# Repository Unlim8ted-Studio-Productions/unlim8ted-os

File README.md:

<div align="center">
<h1>Unlim8ted Phone</h1><p>A custom CM4-based handheld phone project</p>

<br>

<table>
<tr>

<td width="50%">
  
</td>

<td width="50%">
  
</td>

</tr>
</table>

</div>

---

<h2>Overview</h2>

<p>
Unlim8ted Phone is a handheld phone project built around the Raspberry Pi Compute Module 4.
</p>

<p>
This repository contains the hardware, enclosure design, operating system work, and archived PCB development files for the project.
</p>

---

<h2>Repository Layout</h2>

```text
/
├─ 3d/        enclosure, renders, printable parts
├─ docs/      project documentation
├─ os/        Unlim8ted OS source and docs
├─ pcb/       archived PCB design files
└─ README.md
```

---

<h2>Hardware + Cost Breakdown</h2>

<table>

<tr>
<th align="left">Component</th>
<th align="left">Details</th>
<th align="right">Price</th>
</tr>

<tr>
<td>Compute Module</td>
<td>Raspberry Pi CM4 Lite — 8GB RAM</td>
<td align="right">$105.00</td>
</tr>

<tr>
<td>Carrier Board</td>
<td>Waveshare CM4-NANO-C</td>
<td align="right">$29.99</td>
</tr>

<tr>
<td>Display</td>
<td>Waveshare 6.25-inch DSI LCD</td>
<td align="right">$59.99</td>
</tr>

<tr>
<td>Storage</td>
<td>32GB microSD card</td>
<td align="right">$20.00</td>
</tr>

<tr>
<td>Power Board</td>
<td>Seeed LiPo Rider Plus</td>
<td align="right">$4.90</td>
</tr>

<tr>
<td>Battery</td>
<td>3.7V 3000mAh LiPo</td>
<td align="right">$12.49</td>
</tr>

<tr>
<td>Display Cable</td>
<td>15cm double-sided 15-pin DSI cable</td>
<td align="right">Included</td>
</tr>

<tr>
<td>USB Cable</td>
<td>Adafruit USB Type A → USB Type C</td>
<td align="right">$2.95</td>
</tr>

</table>

<br>

<div align="center">

<h1>$235.32</h1>

<sub>Current estimated build total</sub>

</div>

---

<h2>PCB Status</h2>

<p>
The PCB files inside <code>/pcb</code> are archived only.
</p>

<p>
The original custom PCB revision was abandoned in favor of already-manufactured off-the-shelf boards.
</p>

<p>
These files are preserved strictly for reference purposes and should not be used for fabrication or assembly.
</p>

---

<h2>Project Links</h2>

<div align="center">

<a href="./docs/">Documentation</a>

<a href="./os/">OS Source</a>

<a href="./3d/">3D Files</a>

<a href="./pcb/">Archived PCB Files</a>

</div>

---

<div align="center">

<h3>Unlim8ted Studios</h3>

</div>

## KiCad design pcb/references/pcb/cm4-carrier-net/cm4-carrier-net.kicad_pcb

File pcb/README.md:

# PCB Folder

This folder contains outdated and unfinished PCB design work, archived revisions, fabrication output, supporting libraries, and reference material for the phone project. None of the custom PCB files should be fabricated, and ignoring this warning could result in damage.

## Layout

- `custom pcb files/`
  - the KiCad project folders and board files
  - currently includes `phone/`, `phone-part-1/`, and `phone6layer/`
- `libraries/`
  - custom symbol and footprint libraries
  - vendor library imports used by the projects
- `models/`
  - component, enclosure, and vendor-supplied 3D assets
- `fabrication/`
  - gerbers, pick-and-place files, plots, and JLCPCB exports
- `references/`
  - datasheets, diagrams, screenshots, and video captures
- `scripts/`
  - helper scripts used alongside the PCB workflow
- `archives/`
  - backups, candidate revisions, zip bundles, and superseded files

## Working Projects

- `custom pcb files/phone/`
  - main phone schematic project and its exported 3D artifacts
- `custom pcb files/phone6layer/`
  - 6-layer phone board revision
- `custom pcb files/phone-part-1/`
  - partial board split-out

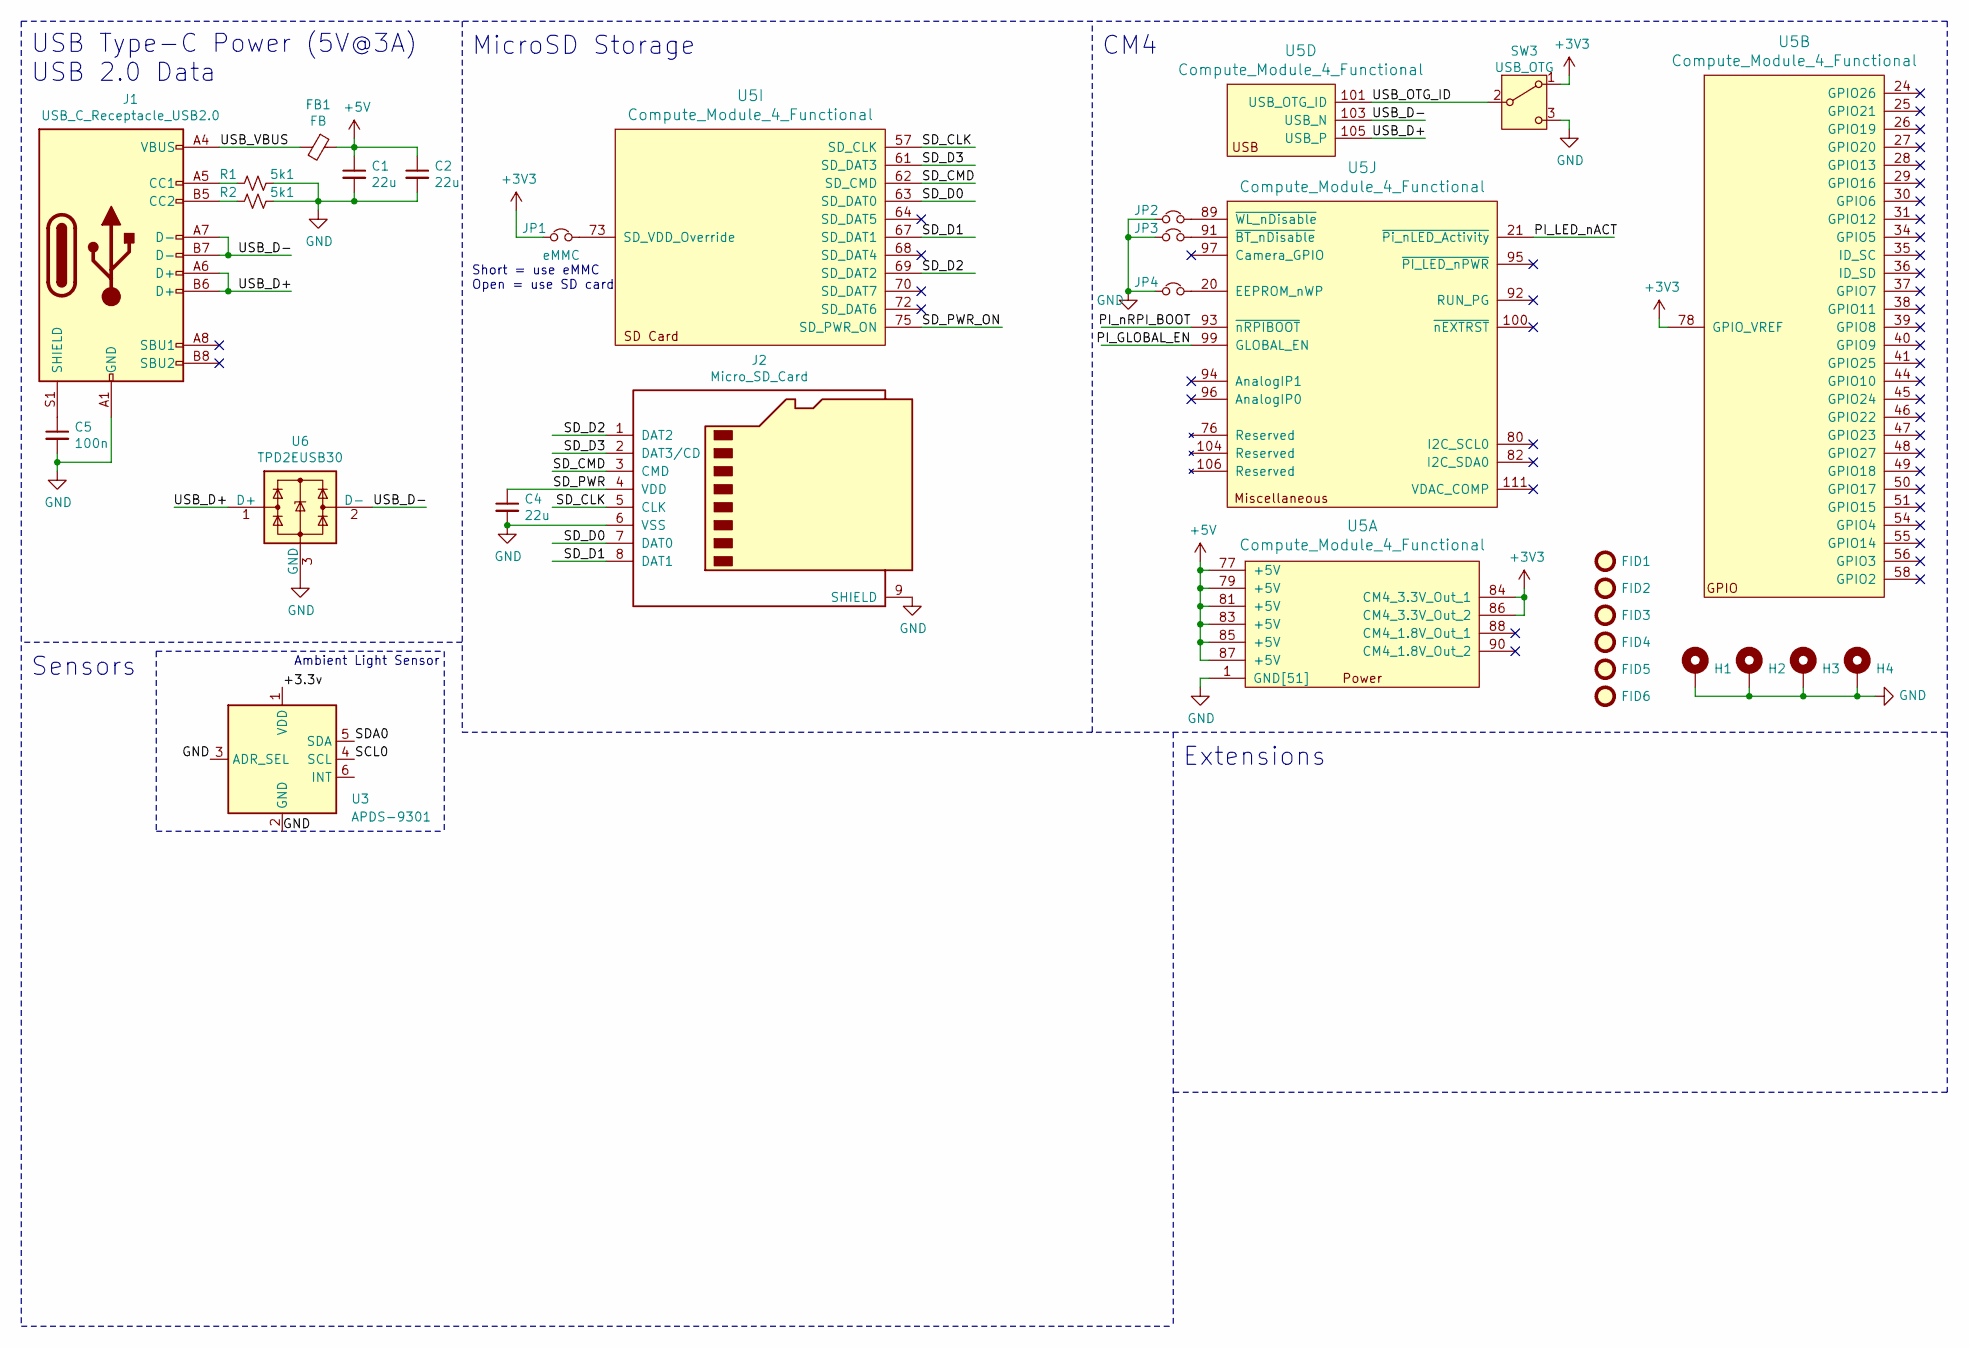
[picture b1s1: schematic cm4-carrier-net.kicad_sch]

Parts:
C1, C2, C4: 22u; C_0805_2012Metric
C5: 100n; C_0805_2012Metric
FB1: FB; L_0805_2012Metric
FID1, FID2, FID3, FID4, FID5, FID6: Fiducial; Fiducial_0.75mm_Mask1.5mm
H1, H2, H3, H4: MountingHole_Pad; MountingHole_2.7mm_M2.5_Pad_Via
J1: USB_C_Receptacle_USB2.0; USB_C_Receptacle_GCT-USB4105
J2: Micro_SD_Card; microSD_HC_Molex_104031-0811
JP1: eMMC; J_Small_NC
JP2: ~WL_nDisable; J_Small_NC
JP3: ~BT_nDisable; J_Small_NC
JP4: EEPROM_nWP; J_Small_NC
R1, R2: 5k1; R_0603_1608Metric
SW3: USB_OTG; SW_SPDT_CK-JS102011SAQN
U3: APDS-9301; Broadcom_APDS-9301
U5: Compute_Module_4_Functional; Raspberry-Pi-4-Compute-Module
U6: TPD2EUSB30; Texas_DRT-3

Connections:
+3V3: JP1.1, SW3.1 (A), U5.78 (GPIO_VREF), U5.84 (CM4_3.3V_Out_1), U5.86 (CM4_3.3V_Out_2)
+5V: C1.1, C2.1, FB1.1, U5.77 (+5V), U5.79 (+5V), U5.81 (+5V), U5.83 (+5V), U5.85 (+5V), U5.87 (+5V)
/+3.3v: U3.1 (VDD)
/PI_GLOBAL_EN: U5.99 (GLOBAL_EN)
/PI_LED_nACT: U5.21 (~Pi_nLED_Activity)
/PI_nRPI_BOOT: U5.93 (~nRPIBOOT)
/SCL0: U3.4 (SCL)
/SDA0: U3.5 (SDA)
/SD_CLK: J2.5 (CLK), U5.57 (SD_CLK)
/SD_CMD: J2.3 (CMD), U5.62 (SD_CMD)
/SD_D0: J2.7 (DAT0), U5.63 (SD_DAT0)
/SD_D1: J2.8 (DAT1), U5.67 (SD_DAT1)
/SD_D2: J2.1 (DAT2), U5.69 (SD_DAT2)
/SD_D3: J2.2 (DAT3/CD), U5.61 (SD_DAT3)
/SD_PWR: C4.1, J2.4 (VDD)
/SD_PWR_ON: U5.75 (SD_PWR_ON)
/USB_D+: J1.A6 (D+), J1.B6 (D+), U5.105 (USB_P), U6.1 (D+)
/USB_D-: J1.A7 (D-), J1.B7 (D-), U5.103 (USB_N), U6.2 (D-)
/USB_OTG_ID: SW3.2 (B), U5.101 (USB_OTG_ID)
/USB_VBUS: FB1.2, J1.A4 (VBUS), J1.A9 (VBUS), J1.B4 (VBUS), J1.B9 (VBUS)
GND: C1.2, C2.2, C4.2, C5.2, H1.1, H2.1, H3.1, H4.1, J1.A1 (GND), J1.A12 (GND), J1.B1 (GND), J1.B12 (GND), J2.6 (VSS), J2.9 (SHIELD), JP2.1, JP3.1, JP4.1, R1.1, R2.1, SW3.3 (C), U3.2 (GND), U3.3 (ADR_SEL), U5.1 (GND[51]), U5.2 (GND[51]), U5.7 (GND[51]), U5.8 (GND[51]), U5.13 (GND[51]), U5.14 (GND[51]), U5.22 (GND[51]), U5.23 (GND[51]), U5.32 (GND[51]), U5.33 (GND[51]), U5.42 (GND[51]), U5.43 (GND[51]), U5.52 (GND[51]), U5.53 (GND[51]), U5.59 (GND[51]), U5.60 (GND[51]), U5.65 (GND[51]), U5.66 (GND[51]), U5.71 (GND[51]), U5.74 (GND[51]), U5.98 (GND[51]), U5.107 (GND[51]), U5.108 (GND[51]), U5.113 (GND[51]), U5.114 (GND[51]), U5.119 (GND[51]), U5.120 (GND[51]), U5.125 (GND[51]), U5.126 (GND[51]), U5.131 (GND[51]), U5.132 (GND[51]), U5.137 (GND[51]), U5.138 (GND[51]), U5.144 (GND[51]), U5.150 (GND[51]), U5.155 (GND[51]), U5.156 (GND[51]), U5.161 (GND[51]), U5.162 (GND[51]), U5.167 (GND[51]), U5.168 (GND[51]), U5.173 (GND[51]), U5.174 (GND[51]), U5.179 (GND[51]), U5.180 (GND[51]), U5.185 (GND[51]), U5.186 (GND[51]), U5.191 (GND[51]), U5.192 (GND[51]), U5.197 (GND[51]), U5.198 (GND[51]), U6.3 (GND)
unnamed: J1.A5 (CC1), R1.2
unnamed: J1.B5 (CC2), R2.2
unnamed: C5.1, J1.S1 (SHIELD)
unnamed: JP1.2, U5.73 (SD_VDD_Override)
unnamed: JP4.2, U5.20 (EEPROM_nWP)
unnamed: JP3.2, U5.91 (~BT_nDisable)
unnamed: JP2.2, U5.89 (~WL_nDisable)

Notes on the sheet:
MicroSD Storage
USB Type-C Power (5V@3A) USB 2.0 Data
Sensors
Ambient Light Sensor
Extensions
CM4
Short = use eMMC Open = use SD card

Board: 4 copper layers, 27 parts (9 on the bottom side), 21 nets, no tracks yet.

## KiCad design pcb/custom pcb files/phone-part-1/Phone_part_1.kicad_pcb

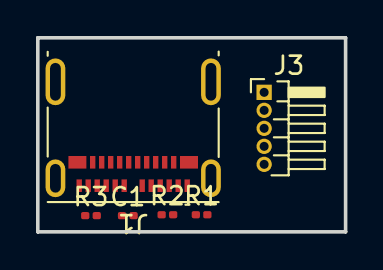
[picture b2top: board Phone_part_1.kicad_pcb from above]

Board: 2 copper layers, 17.1 x 10.8 mm, 6 parts (0 on the bottom side), 7 nets, no tracks yet.

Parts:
C1: 10uF; C_0201_0603Metric
J1: USB_C_Receptacle; USB_C_Receptacle_Molex_105450-0101
J3: Conn_01x05_Pin; PinHeader_1x05_P1.00mm_Horizontal
R1, R2: 5.1K; R_0201_0603Metric
R3: 0 Ω; R_0201_0603Metric

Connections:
/+5v: C1.1, J1.A4 (VBUS), J1.A9 (VBUS), J1.B4 (VBUS), J1.B9 (VBUS), J3.1
/AIN0: J1.A5 (CC1), R1.1
/AIN1: J1.B5 (CC2), R2.1
/USB2_N: J1.A7 (D-), J1.B7 (D-), J3.3
/USB2_P: J1.A6 (D+), J1.B6 (D+), J3.4
GND: C1.2, J1.A1 (GND), J1.A12 (GND), J1.B1 (GND), J1.B12 (GND), J3.2, J3.5, R1.2, R2.2, R3.2
unnamed: J1.S1 (SHIELD), R3.1

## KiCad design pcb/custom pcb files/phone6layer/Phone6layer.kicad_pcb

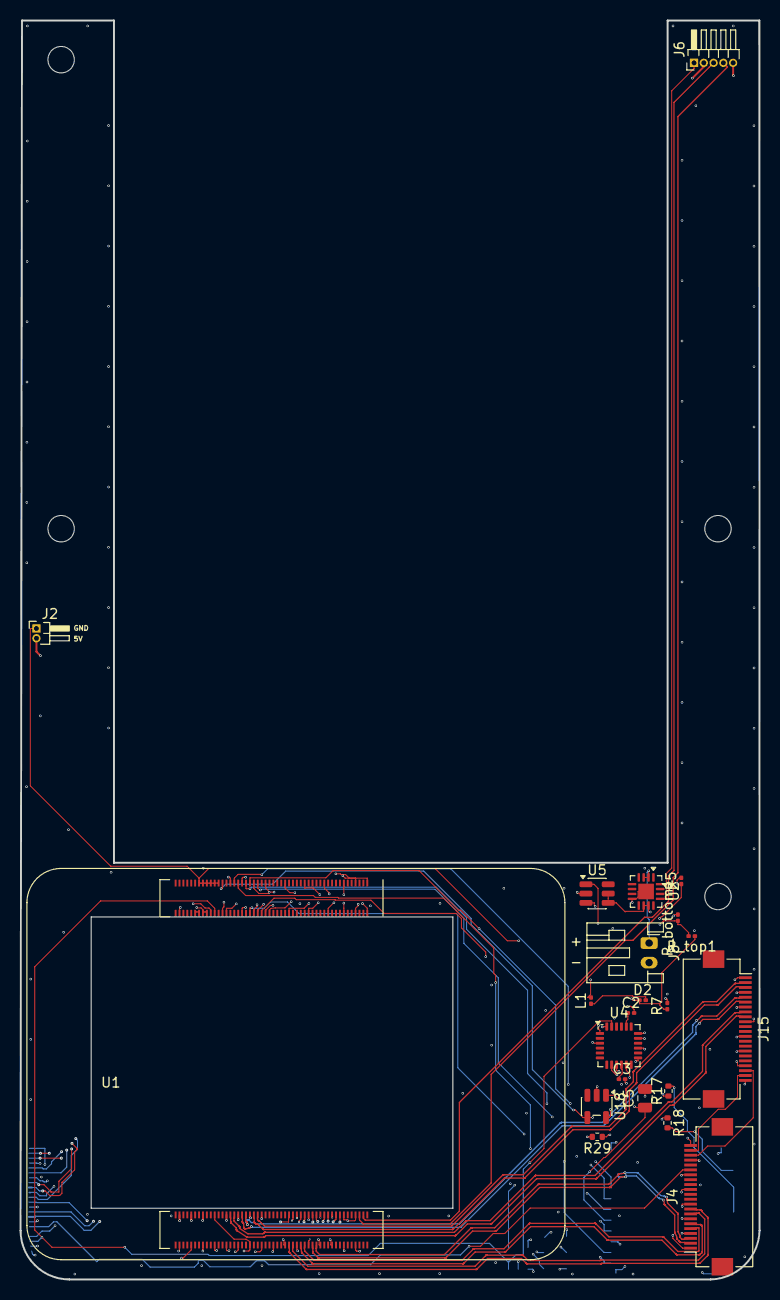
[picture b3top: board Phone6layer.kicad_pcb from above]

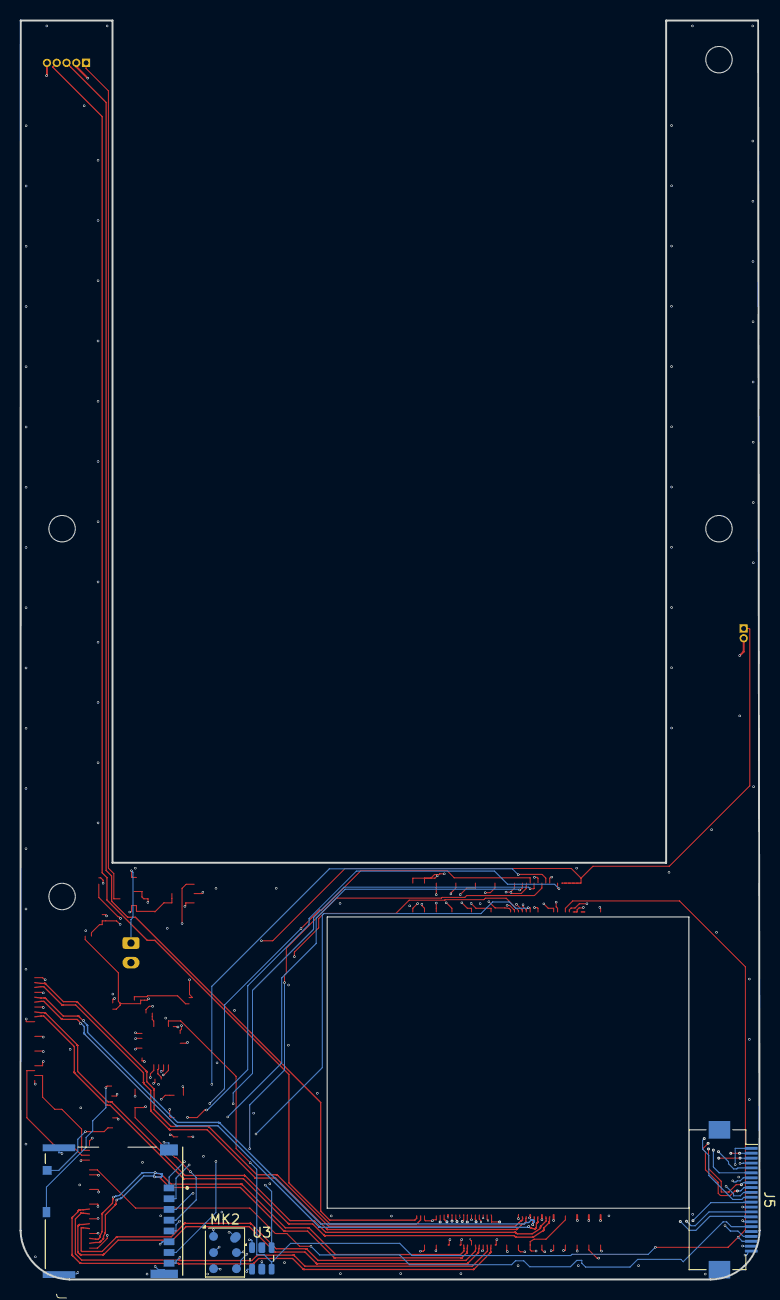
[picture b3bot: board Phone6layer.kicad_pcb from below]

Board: 6 copper layers, 75.5 x 128.7 mm, 26 parts (4 on the bottom side), 55 nets.

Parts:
C2: 2.2 nF; C_0201_0603Metric
C3: 0.1 µF; C_0201_0603Metric
C5: 10u; C_0805_2012Metric
D2: D; D_0201_0603Metric
J2: Conn_01x04_Pin; PinHeader_1x02_P1.00mm_Horizontal
J4, J5, J15: Conn_01x22_Female; Hirose_FH12-22S-0.5SH_1x22-1MP_P0.50mm_Horizontal
J6: Conn_01x05_Pin; PinHeader_1x05_P1.00mm_Horizontal
J7: Micro_SD_Card_Det; SDCARD_MOLEX_503398-1892
J8: Conn_01x02; JST_PH_S2B-PH-K_1x02_P2.00mm_Horizontal
L1: L; L_0201_0603Metric
MK2: MP45DT02; ST_HLGA-6_3.76x4.72mm_P1.65mm
R5, R7: 22 µF; R_0201_0603Metric
R17, R18: nf; R_0402_1005Metric
R29: 12K 1%; R_0402_1005Metric
R_bottom1: 15 kΩ; R_0201_0603Metric
R_top1: 110 kΩ; R_0201_0603Metric
U1: ComputeModule4; Raspberry-Pi-4-Compute-Module-Connector-Phone-Modified
U2: BQ24074RGT; VQFN-16-1EP_3x3mm_P0.5mm_EP1.6x1.6mm
U3: APDS-9301; Broadcom_APDS-9301
U4: MPU-9150; InvenSense_QFN-24_4x4mm_P0.5mm
U5: MT3608; SOT-23-6
U18: RT9742GGJ5; SOT-23-5

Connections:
/+1.8v: U1.88 (+1.8v_(Output)), U1.90 (+1.8v_(Output))
/+3.3v: J4.22, J5.22, J15.22, MK2.6 (VDD), R17.1, R29.1, U1.84 (+3.3v_(Output)), U1.86 (+3.3v_(Output)), U3.1 (VDD), U4.3 (VDD), U4.8 (VLOGIC), U4.13 (VDD), U18.5 (IN)
/+5v: D2.1 (K), J2.1, R7.1, R_top1.1, U1.77 (+5v_(Input)), U1.79 (+5v_(Input)), U1.81 (+5v_(Input)), U1.83 (+5v_(Input)), U1.85 (+5v_(Input)), U1.87 (+5v_(Input))
/CAM0_C_N: J4.8, U1.140 (CAM0_C_N)
/CAM0_C_P: J4.9, U1.142 (CAM0_C_P)
/CAM0_D0_N: J4.2, U1.128 (CAM0_D0_N)
/CAM0_D0_P: J4.3, U1.130 (CAM0_D0_P)
/CAM0_D1_N: J4.5, U1.134 (CAM0_D1_N)
/CAM0_D1_P: J4.6, U1.136 (CAM0_D1_P)
/CAM1_C_N: J5.8, U1.127 (CAM1_C_N)
/CAM1_C_P: J5.9, U1.129 (CAM1_C_P)
/CAM1_D0_N: J5.2, U1.115 (CAM1_D0_N)
/CAM1_D0_P: J5.3, U1.117 (CAM1_D0_P)
/CAM1_D1_N: J5.5, U1.121 (CAM1_D1_N)
/CAM1_D1_P: J5.6, U1.123 (CAM1_D1_P)
/CAM1_D2_N: J5.11, U1.133 (CAM1_D2_N)
/CAM1_D2_P: J5.12, U1.135 (CAM1_D2_P)
/CAM1_D3_N: J5.14, U1.139 (CAM1_D3_N)
/CAM1_D3_P: J5.15, U1.141 (CAM1_D3_P)
/CAM_GPIO: J4.17, J5.17
/DSI0_C_N: J15.8, U1.169 (DSI0_C_N)
/DSI0_C_P: J15.9, U1.171 (DSI0_C_P)
/DSI0_D0_N: J15.2, U1.157 (DSI0_D0_N)
/DSI0_D0_P: J15.3, U1.159 (DSI0_D0_P)
/DSI0_D1_N: J15.5, U1.163 (DSI0_D1_N)
/DSI0_D1_P: J15.6, U1.165 (DSI0_D1_P)
/PCM_CLK: MK2.4 (CLK), U1.54 (GPIO4)
/PCM_DIN: MK2.5 (DOUT), U1.58 (GPIO2)
/PCM_FS: MK2.2 (LR), U1.56 (GPIO3)
/Reserved: R18.1, U1.76 (Reserved)
/SCL0: J5.20, U1.80 (SCL0), U3.4 (SCL), U4.23 (SCL)
/SCL1: J4.20, J15.20
/SDA0: J5.21, U1.82 (SDA0), U3.5 (SDA), U4.24 (SDA)
/SDA1: J4.21, J15.21
/SD_CLK: J7.5 (CLK), U1.57 (SD_CLK)
/SD_CMD: J7.3 (CMD), U1.62 (SD_CMD)
/SD_DAT0: J7.7 (DAT0), U1.63 (SD_DAT0)
/SD_DAT1: J7.8 (DAT1), U1.67 (SD_DAT1)
/SD_DAT2: J7.1 (DAT2), U1.69 (SD_DAT2)
/SD_DAT3: J7.2 (DAT3/CD), U1.61 (SD_DAT3)
/SD_PWR: C5.1, J7.4 (VDD), U18.1 (OUT)
/SD_PWR_ON: R29.2, U1.75 (SD_PWR_ON), U18.4 (EN)
/USB2_N: J6.3, U1.103 (USB2_N)
/USB2_P: J6.4, U1.105 (USB2_P)
/VBUS_RAW: J6.1, U2.13 (IN)
GND: C2.2, C3.2, C5.2, J2.2, J4.1, J4.4, J4.7, J4.10, J4.13, J4.16, J4.19, J5.1, J5.4, J5.7, J5.10, J5.13, J5.16, J5.19, J6.2, J6.5, J7.6 (VSS), J7.11 (SHIELD), J8.2, J15.1, J15.4, J15.7, J15.10, J15.13, J15.16, J15.19, MK2.1 (GND), MK2.3 (GND), R5.2, R7.2, R_bottom1.2, U1.1 (GND), U1.2 (GND), U1.7 (GND), U1.8 (GND), U1.13 (GND), U1.14 (GND), U1.22 (GND), U1.23 (GND), U1.32 (GND), U1.33 (GND), U1.42 (GND), U1.43 (GND), U1.52 (GND), U1.53 (GND), U1.59 (GND), U1.60 (GND), U1.65 (GND), U1.66 (GND), U1.71 (GND), U1.74 (GND), U1.98 (GND), U1.107 (GND), U1.108 (GND), U1.113 (GND), U1.114 (GND), U1.119 (GND), U1.120 (GND), U1.125 (GND), U1.126 (GND), U1.131 (GND), U1.132 (GND), U1.137 (GND), U1.138 (GND), U1.144 (GND), U1.150 (GND), U1.155 (GND), U1.156 (GND), U1.161 (GND), U1.162 (GND), U1.167 (GND), U1.168 (GND), U1.173 (GND), U1.174 (GND), U1.179 (GND), U1.180 (GND), U1.185 (GND), U1.186 (GND), U1.191 (GND), U1.192 (GND), U1.197 (GND), U1.198 (GND), U2.8 (VSS), U2.17 (VSS), U3.2 (GND), U3.3 (ADR_SEL), U4.1 (CLKIN), U4.9 (AD0), U4.11 (FSYNC), U4.15 (GND), U4.17 (GND), U4.18 (GND), U5.2 (GND), U18.2 (GND)
unnamed: D2.2 (A), L1.1
unnamed: J7.10 (DET_A), R17.2
unnamed: J7.9 (DET_B), R18.2
unnamed: J8.1, U2.2 (BAT), U2.3 (BAT)
unnamed: C2.1, U4.20 (CPOUT)
unnamed: C3.1, U4.10 (REGOUT)
unnamed: R5.1, U2.10 (OUT), U2.11 (OUT), U5.4 (EN), U5.5 (IN)
unnamed: R_bottom1.1, R_top1.2, U5.3 (FB)
unnamed: L1.2, U5.1 (SW)

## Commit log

2026-03-29 fix freeze
2026-03-31 fix touch controlls
2026-03-31 update settings, add toggle for debug, and add keyboard
2026-04-01 Initialize README with project details and instructions
    Add detailed project overview, parts list, cost breakdown, and build instructions for the Unlim8ted Phone.
2026-04-01 Update README to improve project overview
    Clarified project description in README.
2026-04-01 Update README to clarify CM4 inclusion
    Clarify that the total includes the CM4 8GB RAM variant, which is not necessarily required.
2026-04-01 Replace 1800mAh battery with 3000mAh in README
    Updated battery specifications and cost breakdown in README.
2026-04-01 add archived pcb assets
2026-04-03 allow scroll in every app by dragging, improve apps and full system theme
2026-04-05 update 3d components model
2026-04-05 update some apps
2026-04-08 add code app
2026-04-08 add build scripts
2026-04-09 Revert "add build scripts"
    This reverts commit d89a7a2b70d2115c7ec0a0d4528cc6cb57167fb3.
2026-04-09 format build scripts and overlay better and simpler
2026-04-09 fix path checke error when building os
2026-04-09 validate some stuff and fix for linux path fail
2026-04-10 faster build process
2026-04-11 fix issues with graphics env init order and update build scripts
2026-04-11 modify build script to be one which presents options (simpler workflow)
2026-04-11 add auto unmount
2026-04-11 fix the CM4 root partition detection for Raspberry Pi OS image, add terminal app, and add default grow mb to build sh
2026-04-12 major changes to the build process and oss
2026-05-27 Added some 3d print case files
2026-05-28 add bottom cover
2026-05-28 fix type c port entrance size
2026-05-28 more casing updates
2026-05-29 add animation
2026-05-29 Revise README.md for clarity and organization
    Update README.md with new formatting and content structure
2026-05-29 Revise README layout and image formatting
    Updated README to include a new table layout and improved image widths.
2026-05-29 updates to overlay
2026-05-29 update docs
2026-05-29 match color theme in readme
2026-05-29 fix 'transparent' gif
2026-05-29 Clean up README formatting and content
    Removed unnecessary line breaks and a paragraph from the README.
2026-05-30 casing updates
2026-06-02 transition to scad and some other tools which kind of didn't work
2026-06-03 Updates to scad
    still working on battery holder
2026-06-03 update an scad file
2026-06-07 lots of work
2026-06-07 get the build script and first os boot working. Still broken DSI
